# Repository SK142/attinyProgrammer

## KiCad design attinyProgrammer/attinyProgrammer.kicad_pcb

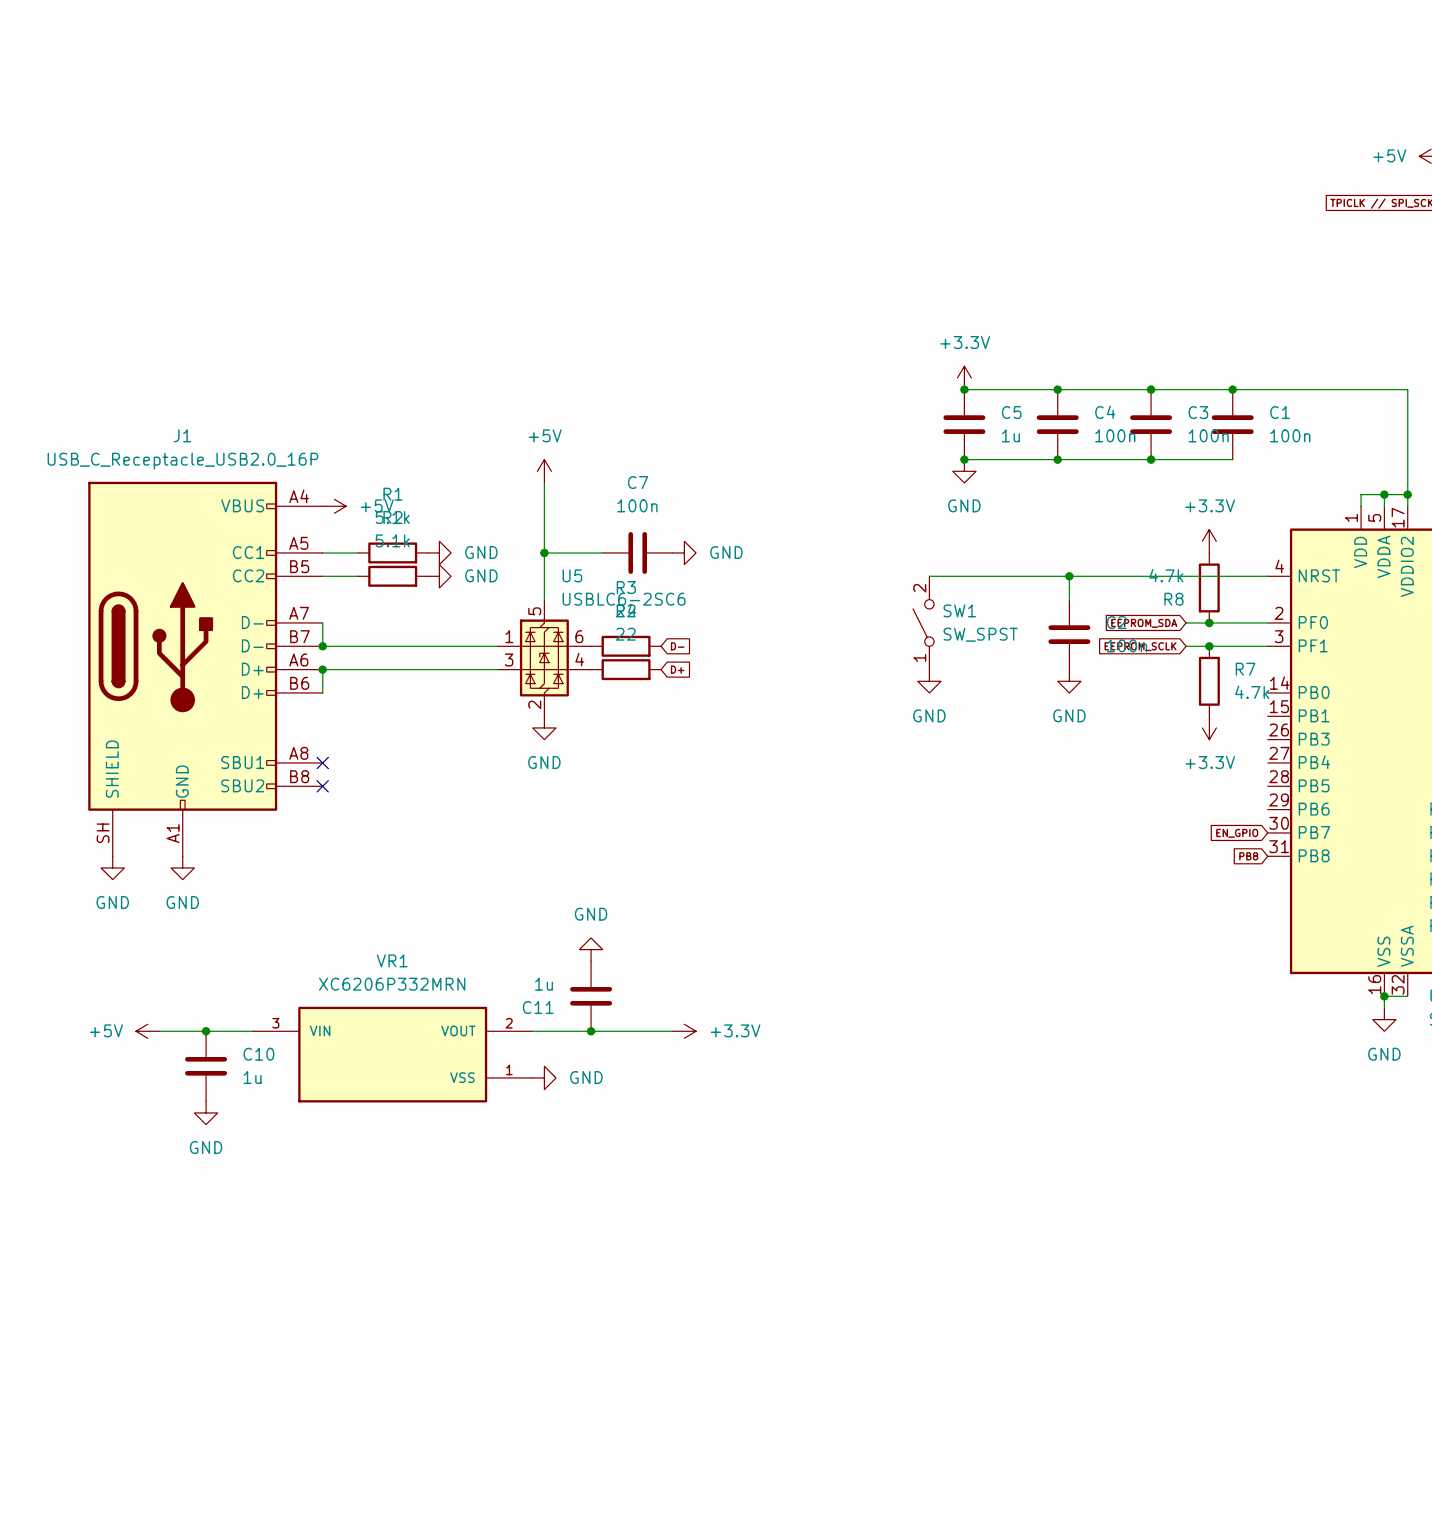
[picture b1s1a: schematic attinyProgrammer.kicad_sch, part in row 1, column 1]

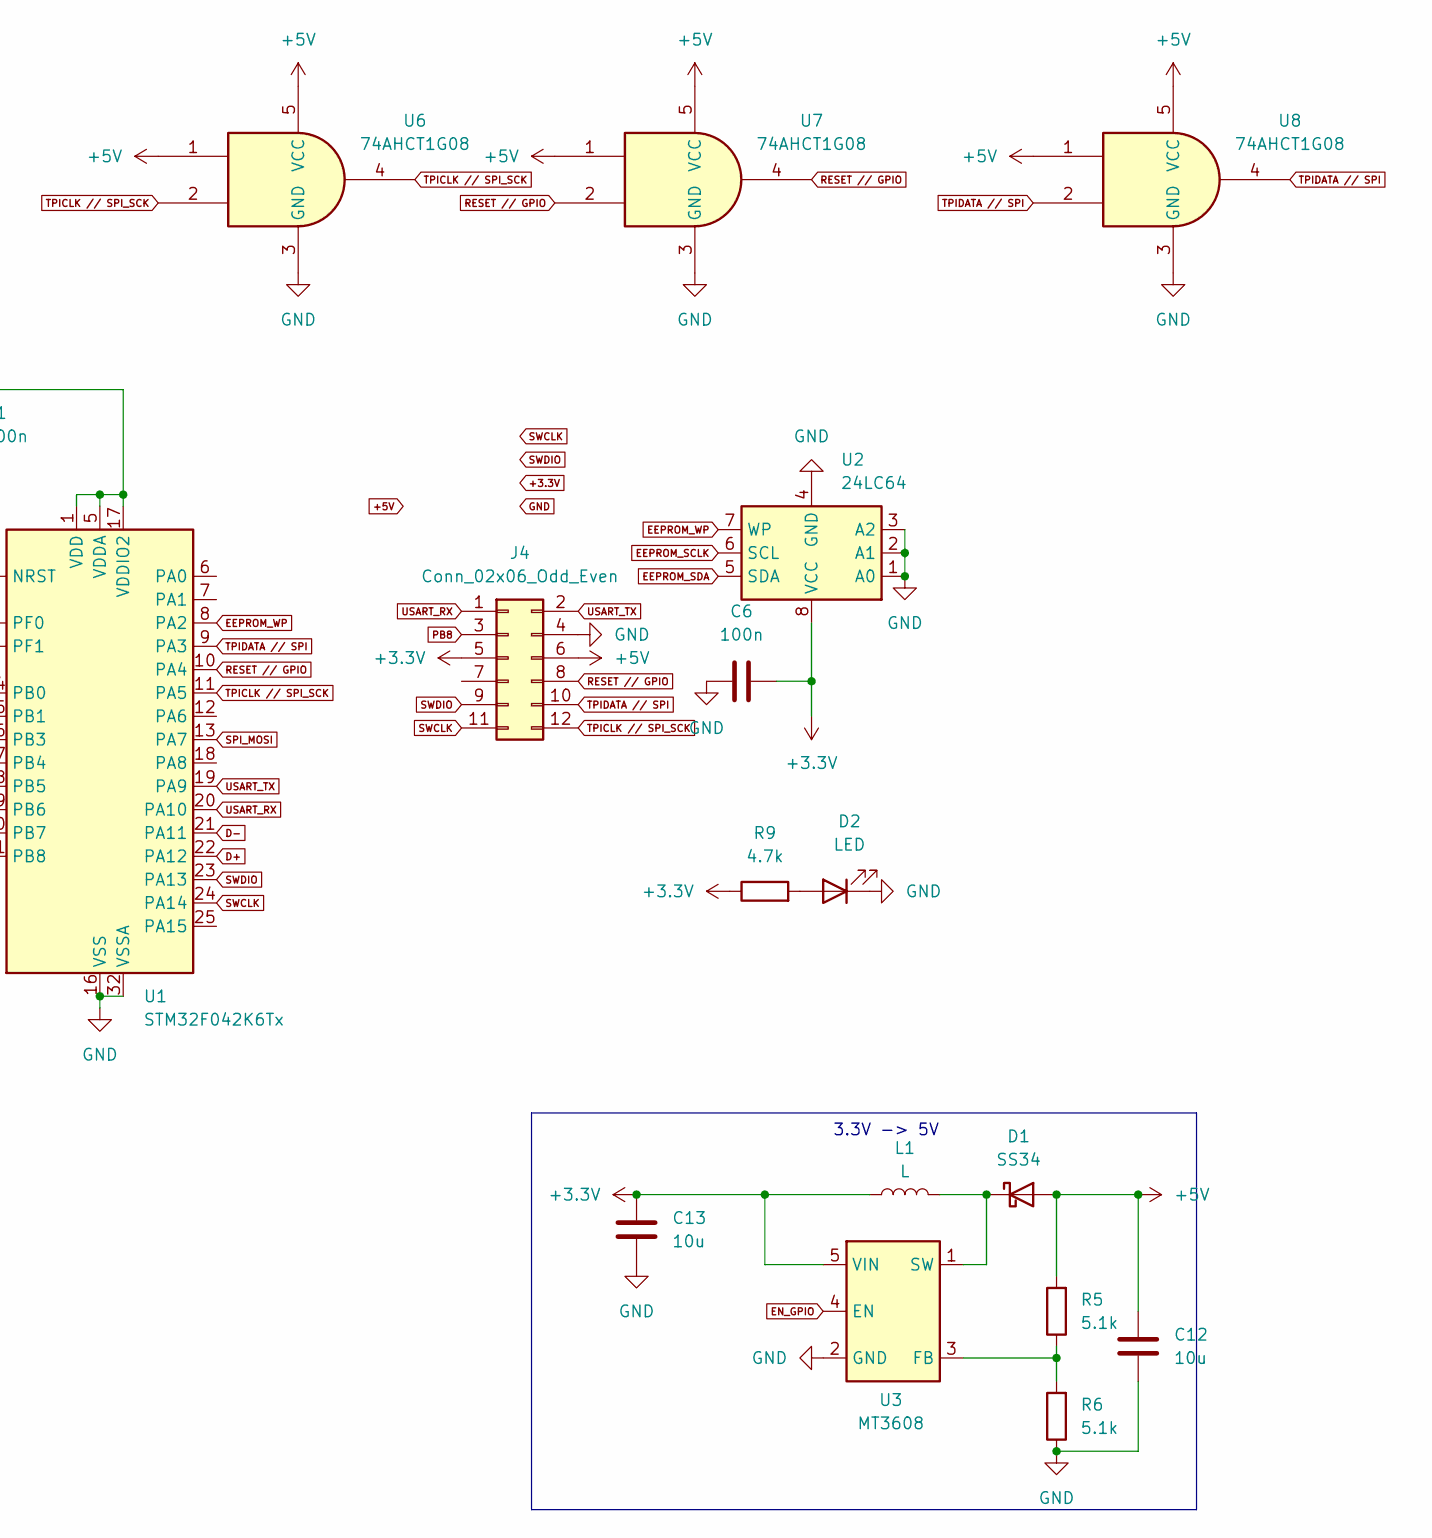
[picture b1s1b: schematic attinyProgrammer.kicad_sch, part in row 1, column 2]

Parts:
C1, C2, C3, C4, C6, C7: 100n; C_0603_1608Metric_Pad1.08x0.95mm_HandSolder
C5, C10, C11: 1u; C_0603_1608Metric_Pad1.08x0.95mm_HandSolder
C12, C13: 10u; C_0603_1608Metric_Pad1.08x0.95mm_HandSolder
D1: SS34; D_SMA
D2: LED; LED_0603_1608Metric_Pad1.05x0.95mm_HandSolder
J1: USB_C_Receptacle_USB2.0_16P; USB_C_Receptacle_GCT_USB4105-xx-A_16P_TopMnt_Horizontal
J4: Conn_02x06_Odd_Even; PinSocket_2x06_P2.54mm_Vertical
L1: L; L_0603_1608Metric_Pad1.05x0.95mm_HandSolder
R1, R2, R5, R6: 5.1k; R_0603_1608Metric_Pad0.98x0.95mm_HandSolder
R3, R4: 22; R_0603_1608Metric_Pad0.98x0.95mm_HandSolder
R7, R8, R9: 4.7k; R_0603_1608Metric_Pad0.98x0.95mm_HandSolder
SW1: SW_SPST; SW_TH_Tactile_Omron_B3F-102x
U1: STM32F042K6Tx; LQFP-32_7x7mm_P0.8mm
U2: 24LC64; SOIC-8_3.9x4.9mm_P1.27mm
U3: MT3608; SOT-23-6
U5: USBLC6-2SC6; SOT-23-6
U6, U7, U8: 74AHCT1G08; SOT23-5
VR1: XC6206P332MRN; VREG_XC6206P332MRN; PARTREV ETR03005-009

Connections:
+3.3V: C1.1, C3.1, C4.1, C5.1, C6.1, C11.1, C13.1, J4.5, L1.1, R7.1, R8.1, R9.1, U1.1 (VDD), U1.5 (VDDA), U1.17 (VDDIO2), U2.8 (VCC), U3.5 (VIN), VR1.2 (VOUT)
+5V: C7.1, C10.1, C12.1, D1.2 (A), J1.A4 (VBUS), J1.A9 (VBUS), J1.B4 (VBUS), J1.B9 (VBUS), J4.6, R5.2, U5.5 (VBUS), U6.1, U6.5 (VCC), U7.1, U7.5 (VCC), U8.1, U8.5 (VCC), VR1.3 (VIN)
D+: R4.2, U1.22 (PA12)
D-: R3.2, U1.21 (PA11)
EEPROM_SCLK: R7.2, U1.3 (PF1), U2.6 (SCL)
EEPROM_SDA: R8.2, U1.2 (PF0), U2.5 (SDA)
EEPROM_WP: U1.8 (PA2), U2.7 (WP)
EN_GPIO: U1.30 (PB7), U3.4 (EN)
GND: C1.2, C2.2, C3.2, C4.2, C5.2, C6.2, C7.2, C10.2, C11.2, C12.2, C13.2, D2.1 (K), J1.A1 (GND), J1.A12 (GND), J1.B1 (GND), J1.B12 (GND), J1.SH (SHIELD), J4.4, R1.2, R2.2, R6.1, SW1.1 (A), U1.16 (VSS), U1.32 (VSSA), U2.1 (A0), U2.2 (A1), U2.3 (A2), U2.4 (GND), U3.2 (GND), U5.2 (GND), U6.3 (GND), U7.3 (GND), U8.3 (GND), VR1.1 (VSS)
unnamed: D1.1 (K), L1.2, U3.1 (SW)
unnamed: D2.2 (A), R9.2
unnamed: J1.A5 (CC1), R1.1
unnamed: J1.B5 (CC2), R2.1
unnamed: J1.A6 (D+), J1.B6 (D+), U5.3 (I/O2)
unnamed: J1.A7 (D-), J1.B7 (D-), U5.1 (I/O1)
unnamed: R3.1, U5.6 (I/O1)
unnamed: R4.1, U5.4 (I/O2)
unnamed: C2.1, SW1.2 (B), U1.4 (NRST)
unnamed: R5.1, R6.2, U3.3 (FB)
PB8: J4.3, U1.31 (PB8)
RESET // GPIO: J4.8, U1.10 (PA4), U7.2, U7.4
SPI_MOSI: U1.13 (PA7)
SWCLK: J4.11, U1.24 (PA14)
SWDIO: J4.9, U1.23 (PA13)
TPICLK // SPI_SCK: J4.12, U1.11 (PA5), U6.2, U6.4
TPIDATA // SPI: J4.10, U1.9 (PA3), U8.2, U8.4
USART_RX: J4.1, U1.20 (PA10)
USART_TX: J4.2, U1.19 (PA9)

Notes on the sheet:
3.3V -> 5V

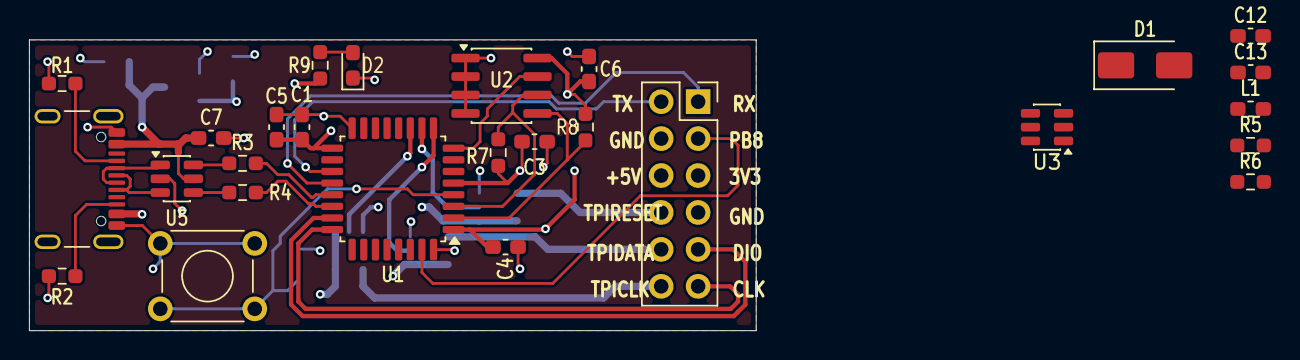
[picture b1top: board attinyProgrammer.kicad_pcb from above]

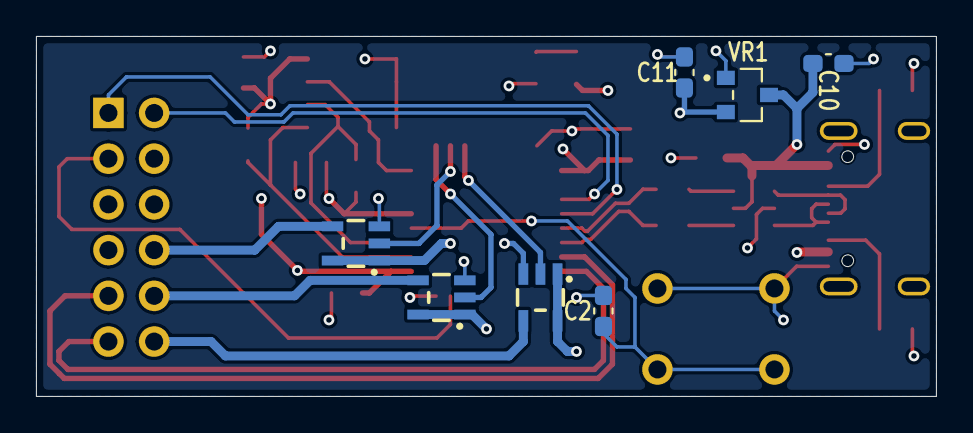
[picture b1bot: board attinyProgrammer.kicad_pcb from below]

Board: 4 copper layers, 50.0 x 20.0 mm, 34 parts (7 on the bottom side), 27 nets.
